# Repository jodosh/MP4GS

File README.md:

MP4GS
=====

This is a collection of programs for an openCV vision system. External 
requirements include openCV2 and uCamArduinoLibrary.

The Python port requires: 
	python 2.7
	openCV2
	pyserial
	numpy
	glob

The NewPing directory is a copy of the arduino library for the Ping sensor on the MP4GS platform
http://playground.arduino.cc/Code/NewPing

If using Anaconda python opencv can be installed using 
```
conda install -c https://conda.binstar.org/menpo opencv
```

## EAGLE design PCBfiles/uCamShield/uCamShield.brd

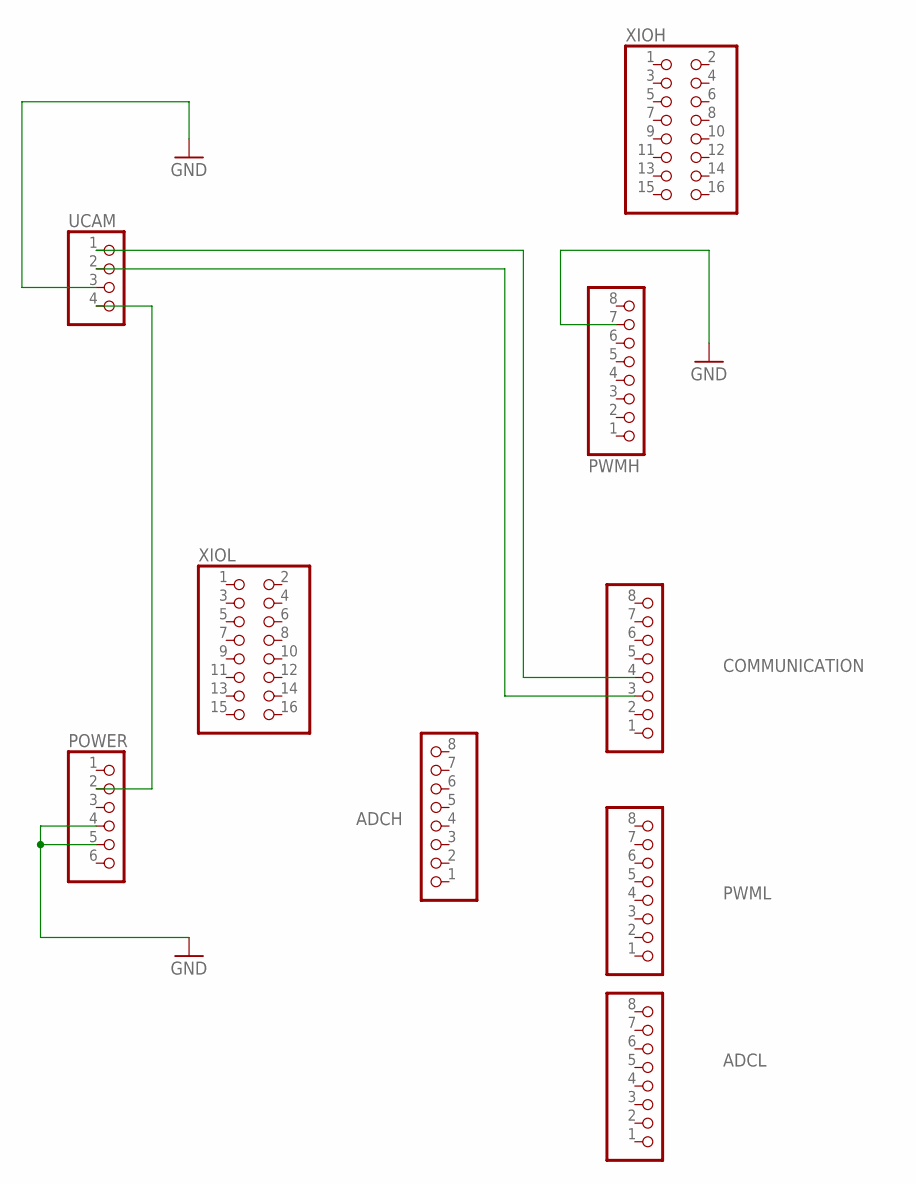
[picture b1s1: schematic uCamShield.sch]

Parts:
ADCH: PINHD-1X8; 1X08
ADCL: PINHD-1X8; 1X08
COMMUNICATION: PINHD-1X8; 1X08
POWER: PINHD-1X6; 1X06
PWMH: PINHD-1X8; 1X08
PWML: PINHD-1X8; 1X08
UCAM: PINHD-1X4; 1X04
XIOH: PINHD-2X8; 2X08
XIOL: PINHD-2X8; 2X08

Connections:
GND: POWER.4, POWER.5, PWMH.7, UCAM.3
unnamed: POWER.2, UCAM.4
unnamed: COMMUNICATION.4, UCAM.1
unnamed: COMMUNICATION.3, UCAM.2

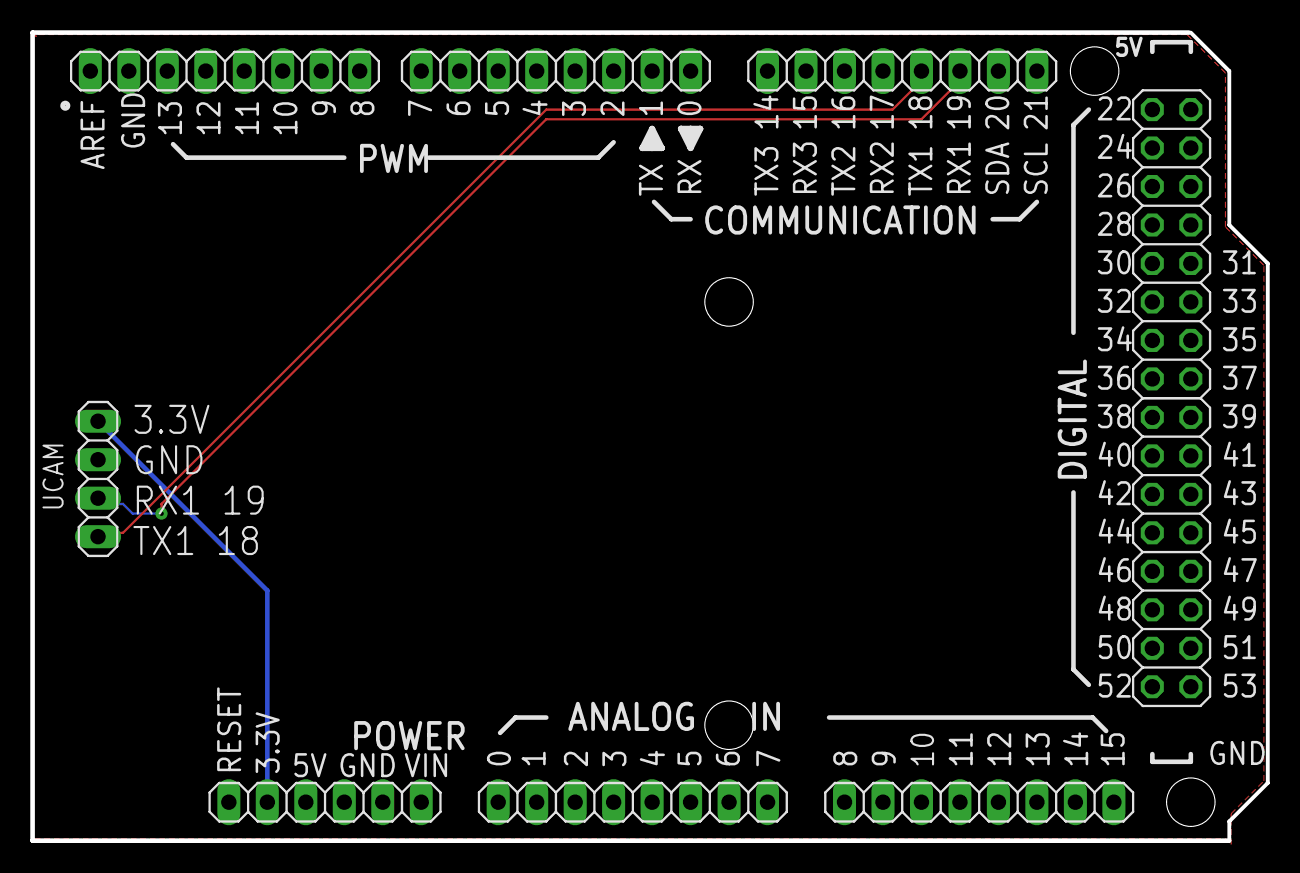
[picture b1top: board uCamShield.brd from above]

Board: 2 copper layers, 81.5 x 53.3 mm, 9 parts (0 on the bottom side), 4 nets.

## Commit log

2014-06-10 calculateDistanceAnAngle source
    source to calculate where a black object is from MP4GS given all needed
    info
2014-07-08 added chessboard files
2014-07-08 readme
    added readme
2014-07-18 added camera Calibration functions
    TODO test and debug more
2015-09-15 python port
2015-09-22 python functionality fixes
    added good image test to camera matrix calculation and undistort image
    to user library
2015-09-22 python capture of images
    The first working example of using python to get the images from the
    arduino (8bitGreyscale)
2015-09-22 readme update
    readme updated for python inclusion
2015-09-23 new python capture modes
2015-09-29 reorginized python files, and added 4bit chessboards
2015-10-13 added arduino shield eagle files and reorg of capture samples
2015-10-19 added ping library, and updated README
2015-10-20 added MD25 Library for motors
2015-10-28 Moved all arduino libraries into a common folder
    The MD25 library needs some work
2015-11-06 Fixed PCB file for uCam shield
2015-11-18 Added Original project files from 2011
2015-12-08 bug fixes
2016-04-09 cpp usage
2016-04-13 distance and angle add
2016-04-14 angle and distance
2016-04-19 undistortExample
2016-04-25 added UndistortExample and begain angle and distance calculation
2016-04-25 added good data set for camera calibration
2016-04-25 added best data set undistort to the example
2016-04-25 dded biModal example
2016-05-04 Remove un-need tracked file
2016-05-04 2bit chessboards capture for camera calibration
2016-05-04 dont want .pyc files
2016-05-04 remove .directory files
2016-05-04 .directory
2016-05-04 removed .directory files
2016-05-05 fixed symlinks for user.py and added file for testing/debugging angleAndDistance
2016-10-17 refactoring examples
2016-10-20 update reame for anaconda opencv install tip
2017-02-20 add final demo
2017-02-20 added final ppt
    started final pt
2017-02-20 fixed location *minor*
2017-03-05 adding Presentation
